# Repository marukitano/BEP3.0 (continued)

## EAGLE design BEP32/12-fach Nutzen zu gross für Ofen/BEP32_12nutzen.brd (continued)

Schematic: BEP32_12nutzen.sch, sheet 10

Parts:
6V9, 10V9: TPSB2.0; B2.0
19, 20: 2081-1132; 12-PIN
C91, C92: 100u; C1206
C93, C100: 100nF,; C0805
C94: 4.7u; C0805
C95, C96: 100nF.; C0805
C97: 2.2nF; C0805
C98, C99: 100nF; C0805
D109, D118: 1N4007; DO-214AC
D110, D111: 1N4007,; DO-214AC
D112, D117: 1N4007.; DO-214AC
D113, D116: 1N5817; DO-214AC_SLIM
D114, D115: 1N5817.; DO-214AC_SLIM
D119: SM6T; DO214AA
D120: SM6TDO214AA_BI; DO214AA_BI
FID37, FID38, FID39, FID40: FIDUCIAL; FIDUCIAL_1MM
IC100: 4028; SO16
IC101: 6V pos; 78LXX
IC102: 317TO202H_NOHOLE; TO220H_NOHOLE
IC103: ULN2004; SO16
IC104: LM339; SO14
IC105: 78L06; SOT89_ROUND
IC106: 555; SO08
IC107: 4538; SO16
IC108: 78L10; SOT89_ROUND
IC109: LM2904; SO08
IC110: NUP4304SOT457_R; SOT457R_PHILIPS
JP46, JP48, JP49, JP50: JP2EJP2_SMALLPADS; JP2_SMALLPADS
JP47: JP2E_ORIG; JP2_ORIG_SMALLPADS
LED55, LED56, LED57, LED58, LED59, LED60: LEDLD260; LD260
Q64, Q67: BA; SOT89
Q65, Q66: BA.; SOT89
Q68: MY; SOT89
Q69, Q70: J1; SOT-23
R415, R417, R449, R450: 47; V235/17_1MM
R416, R439, R440, R459: 13; R1206
R418, R419, R420, R425, R426, R445, R446: 104; R0805
R421, R431, R442: 4701; R0805
R422, R423, R428, R430, R454: 1002; R0805
R424, R427: 1502; R0805
R429, R452: 2201; R0805
R432, R441, R448, R451, R456: 2702; R0805
R433, R438, R455, R457, R458: 102; R0805
R434, R460: R_user; R0805
R435, R443: 100; R0805
R436, R444: (101); R0805
R437: (1000); R0805
R447, R453: (1002); R0805
SJ10: SJ
START9: TPSB2.0; B2.0
TP208, TP209, TP210, TP211, TP212, TP213, TP214, TP215, TP216, TP217, TP218, TP219, TP220, TP221, TP222, TP223, TP224, TP225, TP227, TP228, TP229, TP230: TPSB2.0; B2.0
TP226: TPSB1,27; B1,27
X28: CON_BMWV2; 24-PIN_V2
X29: 22-23-2051
X30: 22-23-2021

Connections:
+10V: 10V9.TP, C98.1, IC106.4 (R), IC106.8 (V+), IC107.3 (CD), IC107.5 (B), IC107.13 (CD), IC107.16 (VDD), IC108.1 (OUT), R451.2; also elsewhere on the board
+12V: 20.1, D119.C, IC100.16 (VDD), IC101.IN, IC103.9 (CD+), IC105.3 (IN), IC108.3 (IN), IC110.2 (V+), JP46.2, Q64.3 (E), Q67.3 (E), R417.2, R418.2, R419.2, R420.2, R439.1, R440.1, R445.1, TP229.TP, X28.6, X29.1; also elsewhere on the board
+12V10: IC109.7 (OUT), R442.1, R456.1
GND: 19.12, C91.2, C92.2, C93.2, C94.2, C95.2, C96.1, C97.1, C98.2, C99.2, C100.2, D117.1 (+), D119.A, D120.A, IC100.8 (VSS), IC100.11 (D), IC101.GND, IC103.8 (GND), IC104.10 (-IN), IC104.11 (+IN), IC104.12 (GND), IC105.2 (GND), IC105.2@1 (GND), IC106.1 (GND), IC107.1 (T1), IC107.4 (A), IC107.8 (VSS), IC107.15 (T1), IC108.2 (GND), IC108.2@1 (GND), IC109.4 (V-), IC110.5 (V-), Q68.3 (E), Q69.2 (S), Q70.2 (S), R422.1, R428.1, R432.1, R433.2, R434.2, R436.2, R444.2, R446.2, R449.1, R450.1, R458.1, R460.2, X28.13, X28.18, X28.23, X29.5, X30.1; also elsewhere on the board
unnamed: R415.2, R417.1
unnamed: 20.9, D113.1 (+), D114.1 (+), JP48.1, JP49.2, TP226.TP
unnamed: IC100.10 (A), IC110.1 (D1), R420.1, X28.4, X29.2
unnamed: IC100.13 (B), IC110.4 (D4), R419.1, X28.3, X29.3
unnamed: D117.2 (-), Q64.2 (C), START9.TP, X28.5
unnamed: IC100.12 (C), IC110.3 (D3), R418.1, X28.2, X29.4
unnamed: 20.7, LED59.A, TP224.TP, X28.8
unnamed: 20.2, D115.2 (-), LED55.K (C), TP219.TP, X28.12
unnamed: 20.3, D114.2 (-), LED56.K (C), TP220.TP, X28.11
unnamed: 20.4, D113.2 (-), LED57.K (C), TP221.TP, X28.10
unnamed: 20.8, D116.2 (-), LED60.K (C), TP225.TP, X28.14
unnamed: 19.9, D110.1 (+), TP216.TP, X28.17
unnamed: 19.11, D111.1 (+), TP218.TP, X28.19
unnamed: D120.C, R421.2, X28.22
unnamed: C94.1, IC109.3 (+IN), R421.1
unnamed: 20.11, IC103.16 (O1), R452.1, R459.2, TP228.TP
unnamed: IC104.1 (OUT), R425.2, R430.2
unnamed: C91.1, R425.1, R426.2
unnamed: C92.1, IC104.4 (-IN), R426.1
unnamed: IC104.5 (+IN), R427.1, R428.2, R429.2
unnamed: D109.1 (+), R429.1
unnamed: C95.1, IC104.9 (+IN), R432.2, R441.2
unnamed: C96.2, IC104.14 (OUT), R431.2
unnamed: Q67.1 (B), R431.1
unnamed: IC100.2 (Q2), IC103.7 (I7)
unnamed: 19.5, IC103.12 (O5), TP212.TP
unnamed: IC100.1 (Q4), IC103.4 (I4)
unnamed: 19.8, Q70.3 (D), TP215.TP
unnamed: 20.10, TP227.TP, X28.15
unnamed: 20.5, D112.2 (-), LED58.K (C), TP222.TP, X28.9
unnamed: D112.1 (+), R415.1
unnamed: IC100.6 (Q5), IC103.3 (I3)
unnamed: 19.4, IC103.10 (O7), TP211.TP
unnamed: IC102.1 (ADJ), R416.1, R423.2, X28.7
unnamed: IC104.6 (-IN), IC104.8 (-IN), R423.1
unnamed: 19.2, Q66.2 (C), TP209.TP
unnamed: 19.1, TP208.TP, X28.1
unnamed: R448.2, X28.16
unnamed: IC100.15 (Q3), IC103.5 (I5)
unnamed: 19.6, IC103.13 (O4), TP213.TP
unnamed: 19.7, IC103.14 (O3), TP214.TP
unnamed: 20.6, JP47.2, TP223.TP
unnamed: LED59.K (C), R436.1
unnamed: LED55.A, LED56.A, LED57.A, LED58.A, LED60.A, R437.1
unnamed: Q64.1 (B), R438.2
unnamed: IC100.3 (Q0), IC103.1 (I1), IC103.2 (I2), Q70.1 (G)
unnamed: IC100.14 (Q1), IC103.6 (I6)
unnamed: 19.3, IC103.11 (O6), TP210.TP
unnamed: Q65.1 (B), Q65.2 (C), Q66.1 (B), R433.1, R434.1, R460.1, X30.2
unnamed: Q66.3 (E), R440.2
unnamed: Q65.3 (E), R439.2
unnamed: IC104.7 (+IN), R424.1, R441.1
unnamed: IC109.2 (-IN), R422.2
unnamed: Q68.1 (B), R442.2
unnamed: Q69.3 (D), R443.2
unnamed: IC102.2 (VO), R416.2
unnamed: IC102.3 (VI), Q67.2 (C)
unnamed: C97.2, D118.2 (-), IC106.2 (TR), IC106.6 (THR), IC110.6 (D2), R446.1
unnamed: IC106.5 (CV), R447.2
unnamed: IC106.3 (Q), IC107.12 (A), R447.1
unnamed: D118.1 (+), R448.1
unnamed: 19.10, D110.2 (-), D111.2 (-), JP50.1, SJ10.1, TP217.TP
unnamed: JP50.2, R449.2, R450.2, SJ10.2
unnamed: IC107.9 (!Q), IC107.11 (B), R453.2
unnamed: C99.1, IC107.14 (T2), R451.1
unnamed: JP46.1, R452.2
unnamed: IC103.15 (O2), R438.1
unnamed: 20.12, R453.1, TP230.TP
unnamed: D115.1 (+), JP48.2
unnamed: D109.2 (-), IC104.2 (OUT), JP47.1, Q69.1 (G), R445.2
unnamed: IC109.1 (OUT), R454.2
unnamed: C100.1, R454.1, R455.1
unnamed: IC109.5 (+IN), R455.2, R456.2
unnamed: IC109.6 (-IN), R457.1, R458.2
unnamed: D116.1 (+), JP49.1
unnamed: JP47.3, R443.1, R444.1
unnamed: R435.1, X28.21
unnamed: Q68.2 (C), R435.2, R459.1
VCC: 6V9.TP, C93.1, IC101.OUT, IC104.3 (V+), IC105.1 (OUT), IC109.8 (V+), R424.2, R427.2, R430.1, R437.2, R457.2; also elsewhere on the board

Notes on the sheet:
6V regulated for Opamps
current source 96mA
ZündungsPlus
Zündugsplus Choke Öldrucklampe Temperaturlampe Ladekontrolllampe Tankgeber (100hm) ABS-Lampe Lampentest Warnlampe Fernlichtlampe Geschwindigkeitssignal Menütaster
DauerPlus Konstant-Strom für LEDs Gang 1 Gang 2 Gang 3 Gang 4 Gang 5 Neutrallampe Blinker rechts Blinker zusammen Blinker links Masse
DauerPlus Batterie 12V (rot weiss) Ganganzeige Signal C (gelb weiss) Ganganzeige Signal B (gelb schwarz) Ganganzeige Signal A (gelb dunkelblau) 12V/350mA zum Starknopf (schwarz grün) Zündungsplus 12V (grün schwarz) Reservelampe (weiss) ABS Leuchte (blau) Ladekontrollleuchte (schaltet auf Masse) (vi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
Masse (braun) Lampentest (schaltet auf Masse)(weiss blau) Fernlichtlampe (12V) (weiss) Drehzahl Zündspule (schwarz blau) Blinker rechts (blau scharz) Masse (braun) Blinker links (blau rot) nicht angeschlossen Tachosiganl zum Blinrelais (balu grün) Tachogeber (gelb) Masse Tachobeger (braun) Tachobel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
4.7V
Stromquelle für Gang LEDs. Für mehr als 12mA muss ein Widerstand "R_user" eingelötet werden. Für weniger muss der 1kOhm SMD Widerstand neben R_user entfernt werden I = 12V/1kOhm(default)+12V/R_user I= 12mA (default) + 12V/R_user Beispiel: R_user Strom in LEDs 1 kOhm 22-26mA ohne 11-13mA
Gang 1
Gang 2
Gang 3
Gang 4
Gang 5
Variante "eine LED leuchtet"
Variante "alle LEDs bis und mit Gang X leuchten"
Klemmleisten Ausgang:
Klemmleisten Ausgang:
an Zündungsplus anhängen (Neutral leuchtet wenn Gang 0 eingelegt und Zündschlüssel steckt )
an Ausgang "Neutrallampe" anhängen
Neutrallampe für eigene Ganganzeige
Externe Beschaltung
Anzeige:
nicht bestückt
rising edge trigger A
BAR
RES
BL resistors

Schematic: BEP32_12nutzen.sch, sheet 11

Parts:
6V10, 10V10: TPSB2.0; B2.0
21, 22: 2081-1132; 12-PIN
C101, C102: 100u; C1206
C103, C110: 100nF,; C0805
C104: 4.7u; C0805
C105, C106: 100nF.; C0805
C107: 2.2nF; C0805
C108, C109: 100nF; C0805
D121, D130: 1N4007; DO-214AC
D122, D123: 1N4007,; DO-214AC
D124, D129: 1N4007.; DO-214AC
D125, D128: 1N5817; DO-214AC_SLIM
D126, D127: 1N5817.; DO-214AC_SLIM
D131: SM6T; DO214AA
D132: SM6TDO214AA_BI; DO214AA_BI
FID41, FID42, FID43, FID44: FIDUCIAL; FIDUCIAL_1MM
IC111: 4028; SO16
IC112: 6V pos; 78LXX
IC113: 317TO202H_NOHOLE; TO220H_NOHOLE
IC114: ULN2004; SO16
IC115: LM339; SO14
IC116: 78L06; SOT89_ROUND
IC117: 555; SO08
IC118: 4538; SO16
IC119: 78L10; SOT89_ROUND
IC120: LM2904; SO08
IC121: NUP4304SOT457_R; SOT457R_PHILIPS
JP51, JP53, JP54, JP55: JP2EJP2_SMALLPADS; JP2_SMALLPADS
JP52: JP2E_ORIG; JP2_ORIG_SMALLPADS
LED61, LED62, LED63, LED64, LED65, LED66: LEDLD260; LD260
Q71, Q74: BA; SOT89
Q72, Q73: BA.; SOT89
Q75: MY; SOT89
Q76, Q77: J1; SOT-23
R461, R463, R495, R496: 47; V235/17_1MM
R462, R485, R486, R505: 13; R1206
R464, R465, R466, R471, R472, R491, R492: 104; R0805
R467, R477, R488: 4701; R0805
R468, R469, R474, R476, R500: 1002; R0805
R470, R473: 1502; R0805
R475, R498: 2201; R0805
R478, R487, R494, R497, R502: 2702; R0805
R479, R484, R501, R503, R504: 102; R0805
R480, R506: R_user; R0805
R481, R489: 100; R0805
R482, R490: (101); R0805
R483: (1000); R0805
R493, R499: (1002); R0805
SJ11: SJ
START10: TPSB2.0; B2.0
TP231, TP232, TP233, TP234, TP235, TP236, TP237, TP238, TP239, TP240, TP241, TP242, TP243, TP244, TP245, TP246, TP247, TP248, TP250, TP251, TP252, TP253: TPSB2.0; B2.0
TP249: TPSB1,27; B1,27
X31: CON_BMWV2; 24-PIN_V2
X32: 22-23-2051
X33: 22-23-2021

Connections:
+10V: 10V10.TP, C108.1, IC117.4 (R), IC117.8 (V+), IC118.3 (CD), IC118.5 (B), IC118.13 (CD), IC118.16 (VDD), IC119.1 (OUT), R497.2; also elsewhere on the board
+12V: 22.1, D131.C, IC111.16 (VDD), IC112.IN, IC114.9 (CD+), IC116.3 (IN), IC119.3 (IN), IC121.2 (V+), JP51.2, Q71.3 (E), Q74.3 (E), R463.2, R464.2, R465.2, R466.2, R485.1, R486.1, R491.1, TP252.TP, X31.6, X32.1; also elsewhere on the board
+12V11: IC120.7 (OUT), R488.1, R502.1
GND: 21.12, C101.2, C102.2, C103.2, C104.2, C105.2, C106.1, C107.1, C108.2, C109.2, C110.2, D129.1 (+), D131.A, D132.A, IC111.8 (VSS), IC111.11 (D), IC112.GND, IC114.8 (GND), IC115.10 (-IN), IC115.11 (+IN), IC115.12 (GND), IC116.2 (GND), IC116.2@1 (GND), IC117.1 (GND), IC118.1 (T1), IC118.4 (A), IC118.8 (VSS), IC118.15 (T1), IC119.2 (GND), IC119.2@1 (GND), IC120.4 (V-), IC121.5 (V-), Q75.3 (E), Q76.2 (S), Q77.2 (S), R468.1, R474.1, R478.1, R479.2, R480.2, R482.2, R490.2, R492.2, R495.1, R496.1, R504.1, R506.2, X31.13, X31.18, X31.23, X32.5, X33.1; also elsewhere on the board
unnamed: R461.2, R463.1
unnamed: 22.9, D125.1 (+), D126.1 (+), JP53.1, JP54.2, TP249.TP
unnamed: IC111.10 (A), IC121.1 (D1), R466.1, X31.4, X32.2
unnamed: IC111.13 (B), IC121.4 (D4), R465.1, X31.3, X32.3
unnamed: D129.2 (-), Q71.2 (C), START10.TP, X31.5
unnamed: IC111.12 (C), IC121.3 (D3), R464.1, X31.2, X32.4
unnamed: 22.7, LED65.A, TP247.TP, X31.8
unnamed: 22.2, D127.2 (-), LED61.K (C), TP242.TP, X31.12
unnamed: 22.3, D126.2 (-), LED62.K (C), TP243.TP, X31.11
unnamed: 22.4, D125.2 (-), LED63.K (C), TP244.TP, X31.10
unnamed: 22.8, D128.2 (-), LED66.K (C), TP248.TP, X31.14
unnamed: 21.9, D122.1 (+), TP239.TP, X31.17
unnamed: 21.11, D123.1 (+), TP241.TP, X31.19
unnamed: D132.C, R467.2, X31.22
unnamed: C104.1, IC120.3 (+IN), R467.1
unnamed: 22.11, IC114.16 (O1), R498.1, R505.2, TP251.TP
unnamed: IC115.1 (OUT), R471.2, R476.2
unnamed: C101.1, R471.1, R472.2
unnamed: C102.1, IC115.4 (-IN), R472.1
unnamed: IC115.5 (+IN), R473.1, R474.2, R475.2
unnamed: D121.1 (+), R475.1
unnamed: C105.1, IC115.9 (+IN), R478.2, R487.2
unnamed: C106.2, IC115.14 (OUT), R477.2
unnamed: Q74.1 (B), R477.1
unnamed: IC111.2 (Q2), IC114.7 (I7)
unnamed: 21.5, IC114.12 (O5), TP235.TP
unnamed: IC111.1 (Q4), IC114.4 (I4)
unnamed: 21.8, Q77.3 (D), TP238.TP
unnamed: 22.10, TP250.TP, X31.15
unnamed: 22.5, D124.2 (-), LED64.K (C), TP245.TP, X31.9
unnamed: D124.1 (+), R461.1
unnamed: IC111.6 (Q5), IC114.3 (I3)
unnamed: 21.4, IC114.10 (O7), TP234.TP
unnamed: IC113.1 (ADJ), R462.1, R469.2, X31.7
unnamed: IC115.6 (-IN), IC115.8 (-IN), R469.1
unnamed: 21.2, Q73.2 (C), TP232.TP
unnamed: 21.1, TP231.TP, X31.1
unnamed: R494.2, X31.16
unnamed: IC111.15 (Q3), IC114.5 (I5)
unnamed: 21.6, IC114.13 (O4), TP236.TP
unnamed: 21.7, IC114.14 (O3), TP237.TP
unnamed: 22.6, JP52.2, TP246.TP
unnamed: LED65.K (C), R482.1
unnamed: LED61.A, LED62.A, LED63.A, LED64.A, LED66.A, R483.1
unnamed: Q71.1 (B), R484.2
unnamed: IC111.3 (Q0), IC114.1 (I1), IC114.2 (I2), Q77.1 (G)
unnamed: IC111.14 (Q1), IC114.6 (I6)
unnamed: 21.3, IC114.11 (O6), TP233.TP
unnamed: Q72.1 (B), Q72.2 (C), Q73.1 (B), R479.1, R480.1, R506.1, X33.2
unnamed: Q73.3 (E), R486.2
unnamed: Q72.3 (E), R485.2
unnamed: IC115.7 (+IN), R470.1, R487.1
unnamed: IC120.2 (-IN), R468.2
unnamed: Q75.1 (B), R488.2
unnamed: Q76.3 (D), R489.2
unnamed: IC113.2 (VO), R462.2
unnamed: IC113.3 (VI), Q74.2 (C)
unnamed: C107.2, D130.2 (-), IC117.2 (TR), IC117.6 (THR), IC121.6 (D2), R492.1
unnamed: IC117.5 (CV), R493.2
unnamed: IC117.3 (Q), IC118.12 (A), R493.1
unnamed: D130.1 (+), R494.1
unnamed: 21.10, D122.2 (-), D123.2 (-), JP55.1, SJ11.1, TP240.TP
unnamed: JP55.2, R495.2, R496.2, SJ11.2
unnamed: IC118.9 (!Q), IC118.11 (B), R499.2
unnamed: C109.1, IC118.14 (T2), R497.1
unnamed: JP51.1, R498.2
unnamed: IC114.15 (O2), R484.1
unnamed: 22.12, R499.1, TP253.TP
unnamed: D127.1 (+), JP53.2
unnamed: D121.2 (-), IC115.2 (OUT), JP52.1, Q76.1 (G), R491.2
unnamed: IC120.1 (OUT), R500.2
unnamed: C110.1, R500.1, R501.1
unnamed: IC120.5 (+IN), R501.2, R502.2
unnamed: IC120.6 (-IN), R503.1, R504.2
unnamed: D128.1 (+), JP54.1
unnamed: JP52.3, R489.1, R490.1
unnamed: R481.1, X31.21
unnamed: Q75.2 (C), R481.2, R505.1
VCC: 6V10.TP, C103.1, IC112.OUT, IC115.3 (V+), IC116.1 (OUT), IC120.8 (V+), R470.2, R473.2, R476.1, R483.2, R503.2; also elsewhere on the board

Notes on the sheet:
6V regulated for Opamps
current source 96mA
ZündungsPlus
Zündugsplus Choke Öldrucklampe Temperaturlampe Ladekontrolllampe Tankgeber (100hm) ABS-Lampe Lampentest Warnlampe Fernlichtlampe Geschwindigkeitssignal Menütaster
DauerPlus Konstant-Strom für LEDs Gang 1 Gang 2 Gang 3 Gang 4 Gang 5 Neutrallampe Blinker rechts Blinker zusammen Blinker links Masse
DauerPlus Batterie 12V (rot weiss) Ganganzeige Signal C (gelb weiss) Ganganzeige Signal B (gelb schwarz) Ganganzeige Signal A (gelb dunkelblau) 12V/350mA zum Starknopf (schwarz grün) Zündungsplus 12V (grün schwarz) Reservelampe (weiss) ABS Leuchte (blau) Ladekontrollleuchte (schaltet auf Masse) (vi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
Masse (braun) Lampentest (schaltet auf Masse)(weiss blau) Fernlichtlampe (12V) (weiss) Drehzahl Zündspule (schwarz blau) Blinker rechts (blau scharz) Masse (braun) Blinker links (blau rot) nicht angeschlossen Tachosiganl zum Blinrelais (balu grün) Tachogeber (gelb) Masse Tachobeger (braun) Tachobel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
4.7V
Stromquelle für Gang LEDs. Für mehr als 12mA muss ein Widerstand "R_user" eingelötet werden. Für weniger muss der 1kOhm SMD Widerstand neben R_user entfernt werden I = 12V/1kOhm(default)+12V/R_user I= 12mA (default) + 12V/R_user Beispiel: R_user Strom in LEDs 1 kOhm 22-26mA ohne 11-13mA
Gang 1
Gang 2
Gang 3
Gang 4
Gang 5
Variante "eine LED leuchtet"
Variante "alle LEDs bis und mit Gang X leuchten"
Klemmleisten Ausgang:
Klemmleisten Ausgang:
an Zündungsplus anhängen (Neutral leuchtet wenn Gang 0 eingelegt und Zündschlüssel steckt )
an Ausgang "Neutrallampe" anhängen
Neutrallampe für eigene Ganganzeige
Externe Beschaltung
Anzeige:
nicht bestückt
rising edge trigger A
BAR
RES
BL resistors

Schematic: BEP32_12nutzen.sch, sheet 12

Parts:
6V11, 10V11: TPSB2.0; B2.0
23, 24: 2081-1132; 12-PIN
C111, C112: 100u; C1206
C113, C120: 100nF,; C0805
C114: 4.7u; C0805
C115, C116: 100nF.; C0805
C117: 2.2nF; C0805
C118, C119: 100nF; C0805
D133, D142: 1N4007; DO-214AC
D134, D135: 1N4007,; DO-214AC
D136, D141: 1N4007.; DO-214AC
D137, D140: 1N5817; DO-214AC_SLIM
D138, D139: 1N5817.; DO-214AC_SLIM
D143: SM6T; DO214AA
D144: SM6TDO214AA_BI; DO214AA_BI
FID45, FID46, FID47, FID48: FIDUCIAL; FIDUCIAL_1MM
IC122: 4028; SO16
IC123: 6V pos; 78LXX
IC124: 317TO202H_NOHOLE; TO220H_NOHOLE
IC125: ULN2004; SO16
IC126: LM339; SO14
IC127: 78L06; SOT89_ROUND
IC128: 555; SO08
IC129: 4538; SO16
IC130: 78L10; SOT89_ROUND
IC131: LM2904; SO08
IC132: NUP4304SOT457_R; SOT457R_PHILIPS
JP56, JP58, JP59, JP60: JP2EJP2_SMALLPADS; JP2_SMALLPADS
JP57: JP2E_ORIG; JP2_ORIG_SMALLPADS
LED67, LED68, LED69, LED70, LED71, LED72: LEDLD260; LD260
Q78, Q81: BA; SOT89
Q79, Q80: BA.; SOT89
Q82: MY; SOT89
Q83, Q84: J1; SOT-23
R507, R509, R541, R542: 47; V235/17_1MM
R508, R531, R532, R551: 13; R1206
R510, R511, R512, R517, R518, R537, R538: 104; R0805
R513, R523, R534: 4701; R0805
R514, R515, R520, R522, R546: 1002; R0805
R516, R519: 1502; R0805
R521, R544: 2201; R0805
R524, R533, R540, R543, R548: 2702; R0805
R525, R530, R547, R549, R550: 102; R0805
R526, R552: R_user; R0805
R527, R535: 100; R0805
R528, R536: (101); R0805
R529: (1000); R0805
R539, R545: (1002); R0805
SJ12: SJ
START11: TPSB2.0; B2.0
TP254, TP255, TP256, TP257, TP258, TP259, TP260, TP261, TP262, TP263, TP264, TP265, TP266, TP267, TP268, TP269, TP270, TP271, TP273, TP274, TP275, TP276: TPSB2.0; B2.0
TP272: TPSB1,27; B1,27
X34: CON_BMWV2; 24-PIN_V2
X35: 22-23-2051
X36: 22-23-2021

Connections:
+10V: 10V11.TP, C118.1, IC128.4 (R), IC128.8 (V+), IC129.3 (CD), IC129.5 (B), IC129.13 (CD), IC129.16 (VDD), IC130.1 (OUT), R543.2; also elsewhere on the board
+12V: 24.1, D143.C, IC122.16 (VDD), IC123.IN, IC125.9 (CD+), IC127.3 (IN), IC130.3 (IN), IC132.2 (V+), JP56.2, Q78.3 (E), Q81.3 (E), R509.2, R510.2, R511.2, R512.2, R531.1, R532.1, R537.1, TP275.TP, X34.6, X35.1; also elsewhere on the board
+12V12: IC131.7 (OUT), R534.1, R548.1
GND: 23.12, C111.2, C112.2, C113.2, C114.2, C115.2, C116.1, C117.1, C118.2, C119.2, C120.2, D141.1 (+), D143.A, D144.A, IC122.8 (VSS), IC122.11 (D), IC123.GND, IC125.8 (GND), IC126.10 (-IN), IC126.11 (+IN), IC126.12 (GND), IC127.2 (GND), IC127.2@1 (GND), IC128.1 (GND), IC129.1 (T1), IC129.4 (A), IC129.8 (VSS), IC129.15 (T1), IC130.2 (GND), IC130.2@1 (GND), IC131.4 (V-), IC132.5 (V-), Q82.3 (E), Q83.2 (S), Q84.2 (S), R514.1, R520.1, R524.1, R525.2, R526.2, R528.2, R536.2, R538.2, R541.1, R542.1, R550.1, R552.2, X34.13, X34.18, X34.23, X35.5, X36.1; also elsewhere on the board
unnamed: R507.2, R509.1
unnamed: 24.9, D137.1 (+), D138.1 (+), JP58.1, JP59.2, TP272.TP
unnamed: IC122.10 (A), IC132.1 (D1), R512.1, X34.4, X35.2
unnamed: IC122.13 (B), IC132.4 (D4), R511.1, X34.3, X35.3
unnamed: D141.2 (-), Q78.2 (C), START11.TP, X34.5
unnamed: IC122.12 (C), IC132.3 (D3), R510.1, X34.2, X35.4
unnamed: 24.7, LED71.A, TP270.TP, X34.8
unnamed: 24.2, D139.2 (-), LED67.K (C), TP265.TP, X34.12
unnamed: 24.3, D138.2 (-), LED68.K (C), TP266.TP, X34.11
unnamed: 24.4, D137.2 (-), LED69.K (C), TP267.TP, X34.10
unnamed: 24.8, D140.2 (-), LED72.K (C), TP271.TP, X34.14
unnamed: 23.9, D134.1 (+), TP262.TP, X34.17
unnamed: 23.11, D135.1 (+), TP264.TP, X34.19
unnamed: D144.C, R513.2, X34.22
unnamed: C114.1, IC131.3 (+IN), R513.1
unnamed: 24.11, IC125.16 (O1), R544.1, R551.2, TP274.TP
unnamed: IC126.1 (OUT), R517.2, R522.2
unnamed: C111.1, R517.1, R518.2
unnamed: C112.1, IC126.4 (-IN), R518.1
unnamed: IC126.5 (+IN), R519.1, R520.2, R521.2
unnamed: D133.1 (+), R521.1
unnamed: C115.1, IC126.9 (+IN), R524.2, R533.2
unnamed: C116.2, IC126.14 (OUT), R523.2
unnamed: Q81.1 (B), R523.1
unnamed: IC122.2 (Q2), IC125.7 (I7)
unnamed: 23.5, IC125.12 (O5), TP258.TP
unnamed: IC122.1 (Q4), IC125.4 (I4)
unnamed: 23.8, Q84.3 (D), TP261.TP
unnamed: 24.10, TP273.TP, X34.15
unnamed: 24.5, D136.2 (-), LED70.K (C), TP268.TP, X34.9
unnamed: D136.1 (+), R507.1
unnamed: IC122.6 (Q5), IC125.3 (I3)
unnamed: 23.4, IC125.10 (O7), TP257.TP
unnamed: IC124.1 (ADJ), R508.1, R515.2, X34.7
unnamed: IC126.6 (-IN), IC126.8 (-IN), R515.1
unnamed: 23.2, Q80.2 (C), TP255.TP
unnamed: 23.1, TP254.TP, X34.1
unnamed: R540.2, X34.16
unnamed: IC122.15 (Q3), IC125.5 (I5)
unnamed: 23.6, IC125.13 (O4), TP259.TP
unnamed: 23.7, IC125.14 (O3), TP260.TP
unnamed: 24.6, JP57.2, TP269.TP
unnamed: LED71.K (C), R528.1
unnamed: LED67.A, LED68.A, LED69.A, LED70.A, LED72.A, R529.1
unnamed: Q78.1 (B), R530.2
unnamed: IC122.3 (Q0), IC125.1 (I1), IC125.2 (I2), Q84.1 (G)
unnamed: IC122.14 (Q1), IC125.6 (I6)
unnamed: 23.3, IC125.11 (O6), TP256.TP
unnamed: Q79.1 (B), Q79.2 (C), Q80.1 (B), R525.1, R526.1, R552.1, X36.2
unnamed: Q80.3 (E), R532.2
unnamed: Q79.3 (E), R531.2
unnamed: IC126.7 (+IN), R516.1, R533.1
unnamed: IC131.2 (-IN), R514.2
unnamed: Q82.1 (B), R534.2
unnamed: Q83.3 (D), R535.2
unnamed: IC124.2 (VO), R508.2
unnamed: IC124.3 (VI), Q81.2 (C)
unnamed: C117.2, D142.2 (-), IC128.2 (TR), IC128.6 (THR), IC132.6 (D2), R538.1
unnamed: IC128.5 (CV), R539.2
unnamed: IC128.3 (Q), IC129.12 (A), R539.1
unnamed: D142.1 (+), R540.1
unnamed: 23.10, D134.2 (-), D135.2 (-), JP60.1, SJ12.1, TP263.TP
unnamed: JP60.2, R541.2, R542.2, SJ12.2
unnamed: IC129.9 (!Q), IC129.11 (B), R545.2
unnamed: C119.1, IC129.14 (T2), R543.1
unnamed: JP56.1, R544.2
unnamed: IC125.15 (O2), R530.1
unnamed: 24.12, R545.1, TP276.TP
unnamed: D139.1 (+), JP58.2
unnamed: D133.2 (-), IC126.2 (OUT), JP57.1, Q83.1 (G), R537.2
unnamed: IC131.1 (OUT), R546.2
unnamed: C120.1, R546.1, R547.1
unnamed: IC131.5 (+IN), R547.2, R548.2
unnamed: IC131.6 (-IN), R549.1, R550.2
unnamed: D140.1 (+), JP59.1
unnamed: JP57.3, R535.1, R536.1
unnamed: R527.1, X34.21
unnamed: Q82.2 (C), R527.2, R551.1
VCC: 6V11.TP, C113.1, IC123.OUT, IC126.3 (V+), IC127.1 (OUT), IC131.8 (V+), R516.2, R519.2, R522.1, R529.2, R549.2; also elsewhere on the board

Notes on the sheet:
6V regulated for Opamps
current source 96mA
ZündungsPlus
Zündugsplus Choke Öldrucklampe Temperaturlampe Ladekontrolllampe Tankgeber (100hm) ABS-Lampe Lampentest Warnlampe Fernlichtlampe Geschwindigkeitssignal Menütaster
DauerPlus Konstant-Strom für LEDs Gang 1 Gang 2 Gang 3 Gang 4 Gang 5 Neutrallampe Blinker rechts Blinker zusammen Blinker links Masse
DauerPlus Batterie 12V (rot weiss) Ganganzeige Signal C (gelb weiss) Ganganzeige Signal B (gelb schwarz) Ganganzeige Signal A (gelb dunkelblau) 12V/350mA zum Starknopf (schwarz grün) Zündungsplus 12V (grün schwarz) Reservelampe (weiss) ABS Leuchte (blau) Ladekontrollleuchte (schaltet auf Masse) (vi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
Masse (braun) Lampentest (schaltet auf Masse)(weiss blau) Fernlichtlampe (12V) (weiss) Drehzahl Zündspule (schwarz blau) Blinker rechts (blau scharz) Masse (braun) Blinker links (blau rot) nicht angeschlossen Tachosiganl zum Blinrelais (balu grün) Tachogeber (gelb) Masse Tachobeger (braun) Tachobel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
4.7V
Stromquelle für Gang LEDs. Für mehr als 12mA muss ein Widerstand "R_user" eingelötet werden. Für weniger muss der 1kOhm SMD Widerstand neben R_user entfernt werden I = 12V/1kOhm(default)+12V/R_user I= 12mA (default) + 12V/R_user Beispiel: R_user Strom in LEDs 1 kOhm 22-26mA ohne 11-13mA
Gang 1
Gang 2
Gang 3
Gang 4
Gang 5
Variante "eine LED leuchtet"
Variante "alle LEDs bis und mit Gang X leuchten"
Klemmleisten Ausgang:
Klemmleisten Ausgang:
an Zündungsplus anhängen (Neutral leuchtet wenn Gang 0 eingelegt und Zündschlüssel steckt )
an Ausgang "Neutrallampe" anhängen
Neutrallampe für eigene Ganganzeige
Externe Beschaltung
Anzeige:
nicht bestückt
rising edge trigger A
BAR
RES
BL resistors

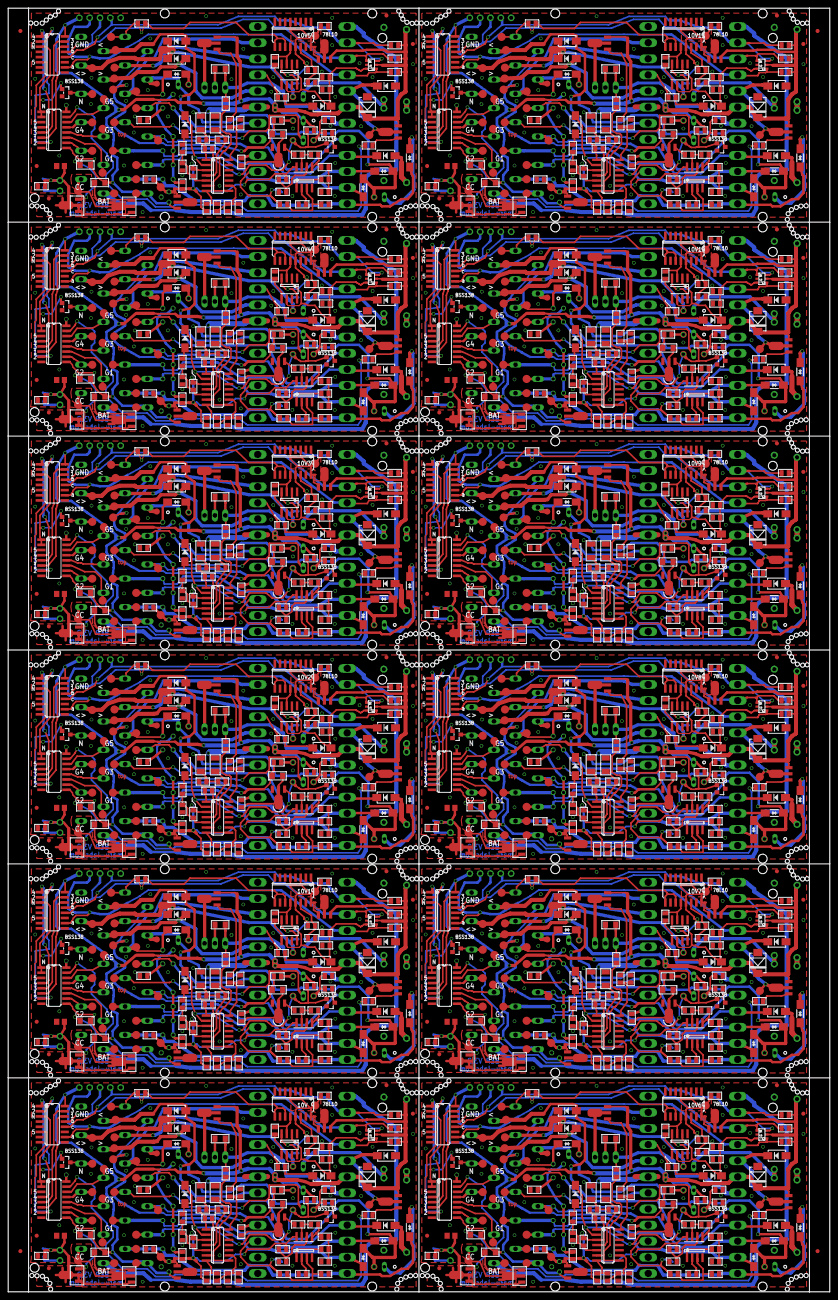
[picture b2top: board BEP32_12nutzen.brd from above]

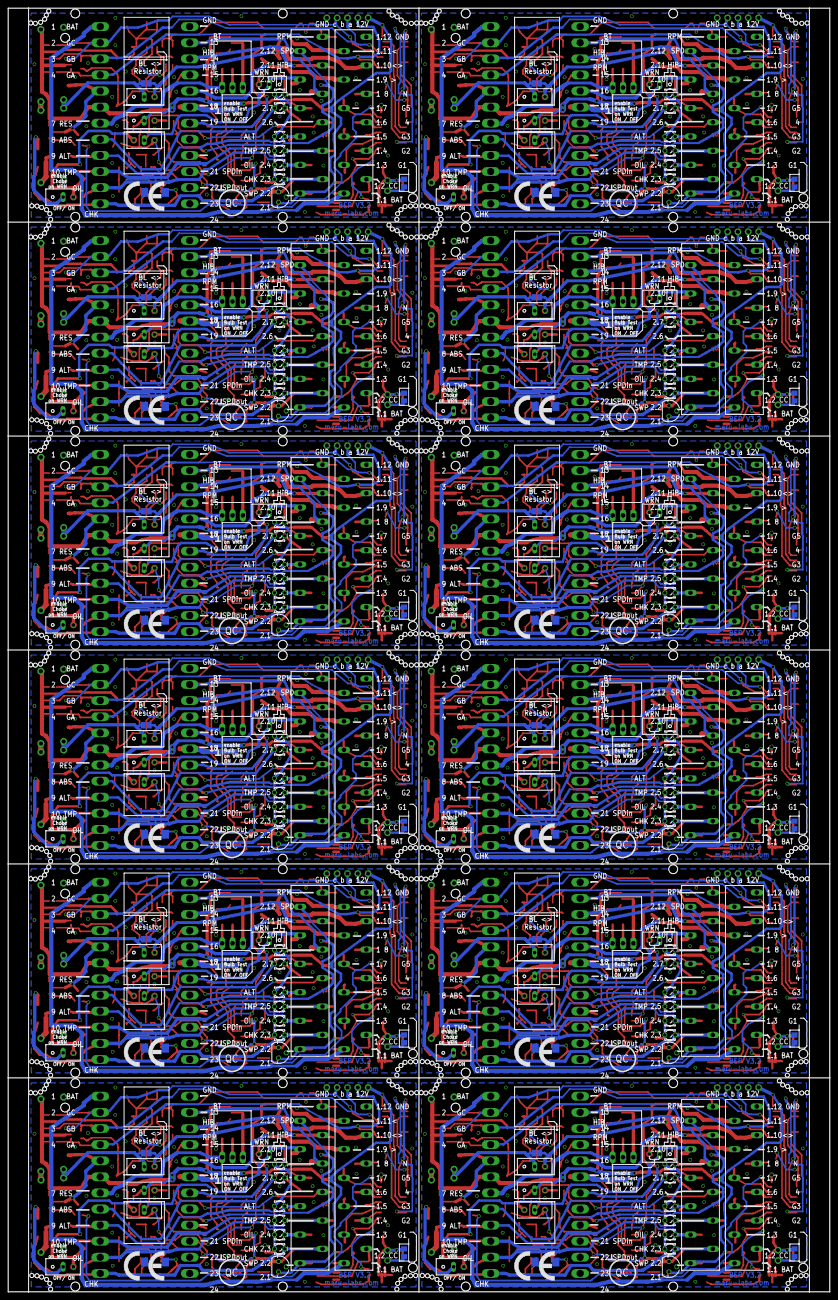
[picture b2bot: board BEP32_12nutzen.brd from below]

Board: 2 copper layers, 202.0 x 315.6 mm, 1612 parts (312 on the bottom side), 952 nets.

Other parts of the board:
U$1, U$2, U$3, U$4, U$5, U$6, U$7, U$8, U$9, U$10, U$11, U$12: CE_10.00
